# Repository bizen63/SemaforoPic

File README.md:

# SemaforoPic
Cruce mediante semáforos con PIC16F84A programado con MicroC y MPLABIPE, simulado con Proteus y grabado con PICKit 3.
Contiene todos los ficheros necesarios para su simulación e implementación.

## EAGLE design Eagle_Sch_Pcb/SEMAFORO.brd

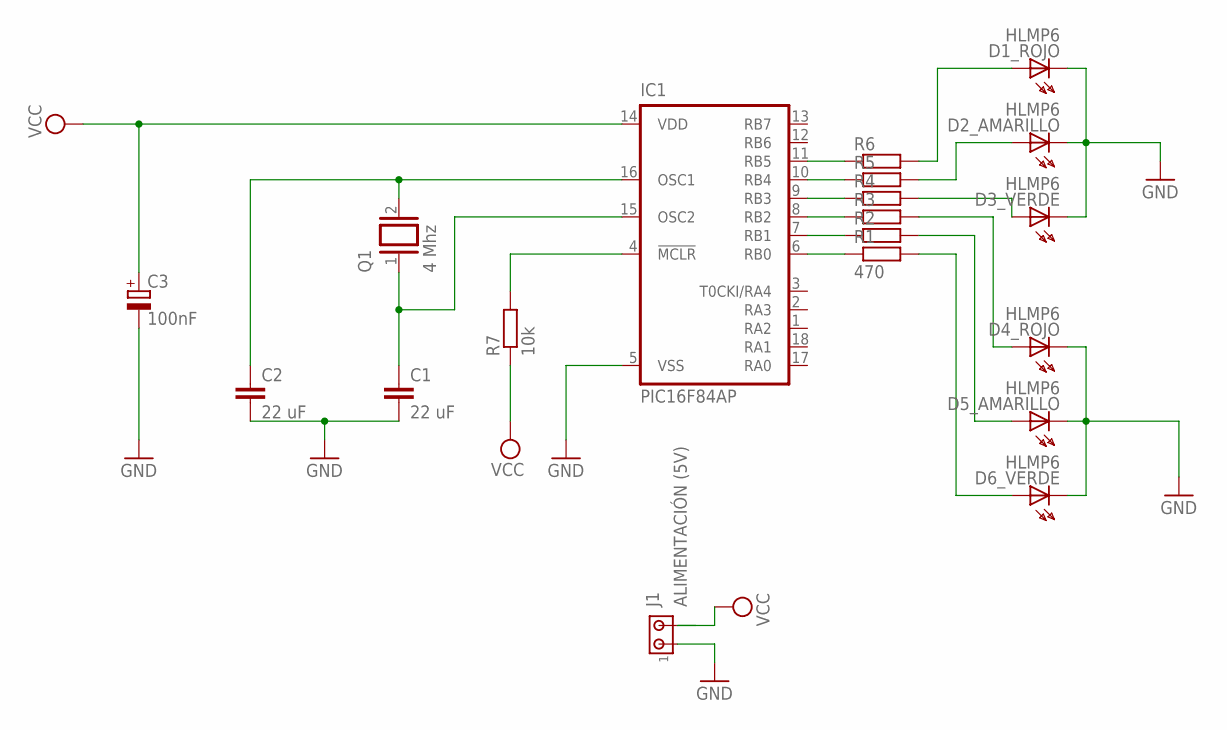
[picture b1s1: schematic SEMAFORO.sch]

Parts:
C1, C2: 22 uF; C2.5-2
C3: 100nF; E1,8-4
D1_ROJO, D2_AMARILLO, D3_VERDE, D4_ROJO, D5_AMARILLO, D6_VERDE: HLMP6
IC1: PIC16F84AP; DIL18
J1: ALIMENTACIÓN (5V); 10X02MTA
Q1: 4 Mhz; QS
R1: 470; 0207/10
R2, R3, R4, R5, R6: R0207/10; 0207/10
R7: 10k; 0207/10

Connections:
GND: C1.2, C2.2, C3.-, D1_ROJO.K, D2_AMARILLO.K, D3_VERDE.K, D4_ROJO.K, D5_AMARILLO.K, D6_VERDE.K, IC1.5 (VSS), J1.1
unnamed: C1.1, IC1.15 (OSC2), Q1.1
unnamed: C2.1, IC1.16 (OSC1), Q1.2
unnamed: D2_AMARILLO.A, R5.2
unnamed: IC1.6 (RB0), R1.1
unnamed: IC1.7 (RB1), R2.1
unnamed: IC1.8 (RB2), R3.1
unnamed: IC1.9 (RB3), R4.1
unnamed: IC1.10 (RB4), R5.1
unnamed: IC1.11 (RB5), R6.1
unnamed: D3_VERDE.A, R4.2
unnamed: D1_ROJO.A, R6.2
unnamed: D4_ROJO.A, R3.2
unnamed: D5_AMARILLO.A, R2.2
unnamed: D6_VERDE.A, R1.2
unnamed: IC1.4 (!MCLR), R7.2
VCC: C3.+, IC1.14 (VDD), J1.2, R7.1

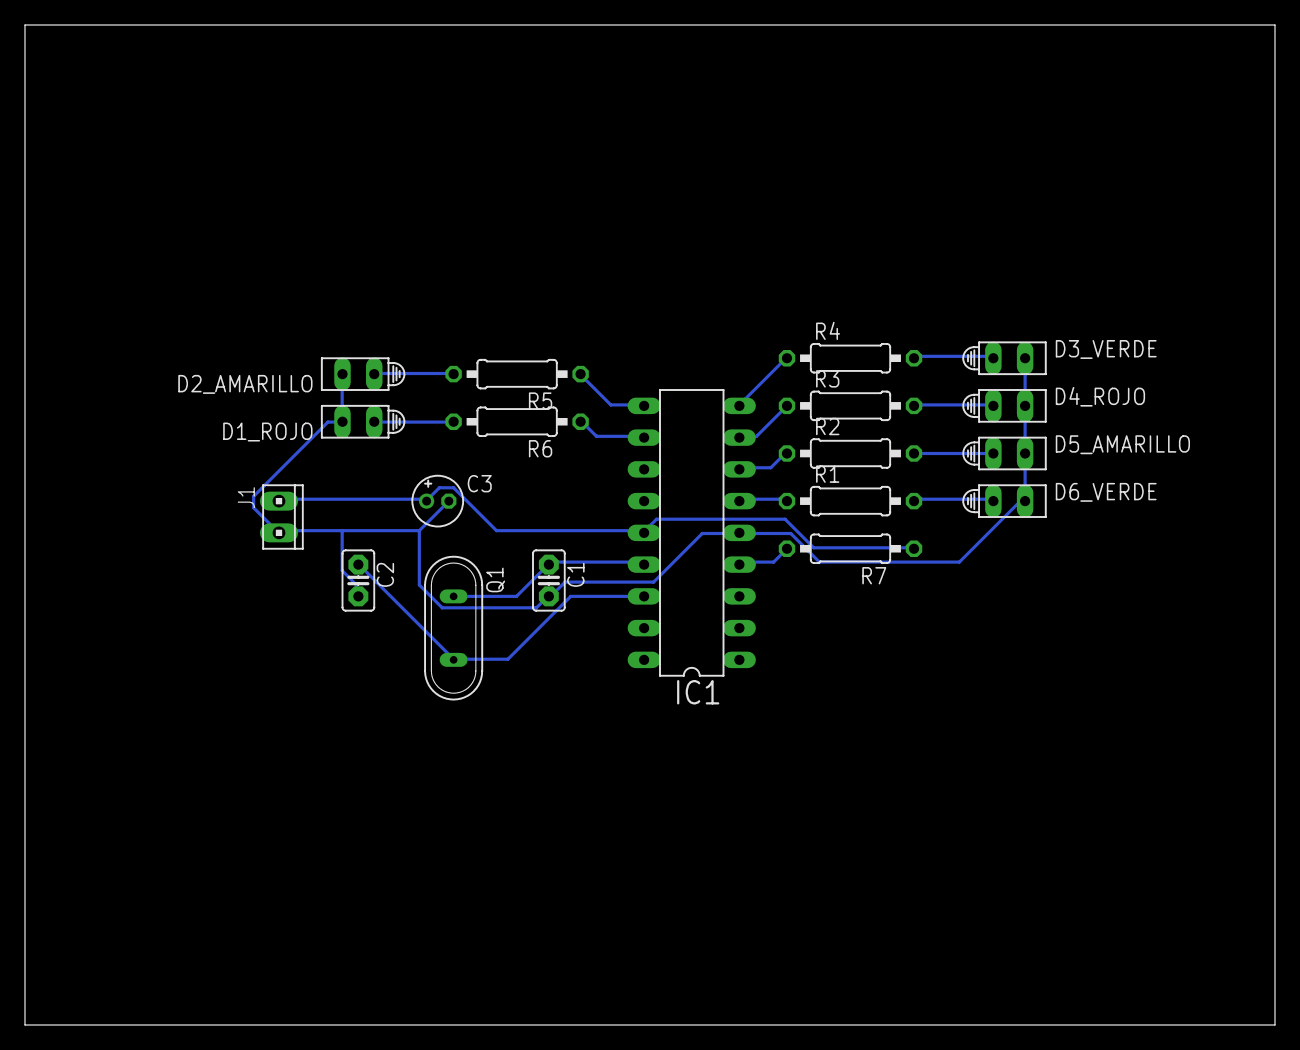
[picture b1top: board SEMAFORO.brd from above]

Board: 2 copper layers, 100.0 x 80.0 mm, 19 parts (0 on the bottom side), 17 nets.

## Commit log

2015-08-25 :boom::camel: Added .gitattributes & .gitignore files
2015-08-25 Cruce mediante semáforos con PIC16F84A
    Cruce mediante semáforos con PIC16F84A programado con MicroC y MPLABIPE,
    simulado con Proteus y grabado con PICKit 3.
2015-08-27 Diseño de esquema y placa con Eagle PCB
    Diseño de esquema y placa con Eagle PCB
